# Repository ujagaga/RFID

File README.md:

RFID reader project for AtTiny2313

The RFID library is based on Addicore arduino library. I re-wrote it as pure C library and removed 
everything not esential to bare reading of an RFID TAG id to reduce the code size.

The initial commit contains a basic example of reading a tag and outputting the 4 bytes of id to UART.

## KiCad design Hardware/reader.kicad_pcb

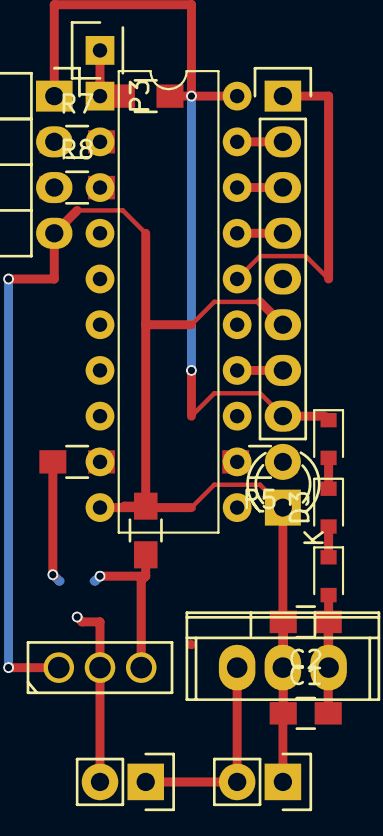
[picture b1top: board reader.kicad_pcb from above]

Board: 2 copper layers, 21 parts (1 on the bottom side), 22 nets.

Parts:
C1: 100n; C_0805_HandSoldering
C2: 10u; C_0805_HandSoldering
D1: LED; LED-3MM
D2, D3, D4: D; D_0805
IC1: ATTINY2313-P; DIP-20_W7.62mm
P1: RST; Socket_Strip_Straight_1x01
P3: UART connector; Socket_Strip_Angled_1x04
P4: Lock; Socket_Strip_Straight_1x02
P6: CONN_01X08; Socket_Strip_Straight_1x08
P7: +12V PWR; Socket_Strip_Straight_1x02
Q1: BC817-40; SOT-23
Q2: BD237; SOT126_SOT32_Housing_Vertical
R3, R6: 10K; R_0805_HandSoldering
R4: 1K; R_0805_HandSoldering
R5, R7, R8: 220R; R_0805_HandSoldering
U1: LM7805CT; TO-220

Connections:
+12V: P4.1, P7.2, U1.1
GNDREF: C1.1, C2.2, D1.1, IC1.10, P3.4, P6.6, P7.1, Q2.1, R6.1, U1.2
unnamed: C1.2, C2.1, D2.2, U1.3
unnamed: D1.2, R5.1
unnamed: D2.1, D3.2
unnamed: D3.1, D4.2
unnamed: D4.1, IC1.20, P3.1, P6.8, R3.2
unnamed: IC1.1, P1.1, R3.1
unnamed: IC1.2, R7.2
unnamed: IC1.3, R8.2
unnamed: IC1.9, R4.2
unnamed: IC1.12, R5.2
unnamed: IC1.14, P6.7
unnamed: IC1.16, P6.1
unnamed: IC1.17, P6.4
unnamed: IC1.18, P6.3
unnamed: IC1.19, P6.2
unnamed: P3.2, R7.1
unnamed: P3.3, R8.1
unnamed: P4.2, Q1.3, Q2.2
unnamed: Q1.1, R4.1
unnamed: Q1.2, Q2.3, R6.2

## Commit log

2017-01-12 RFID reader basic HW and FW
2017-01-12 * EEPROM copy device HW and FW * administration python scripts for EEPROM reader and RFID reader * Python scripts bundled into standalone apps for both Linux and Win
